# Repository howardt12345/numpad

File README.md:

# [numpad](https://kb.ht12345.xyz/np0)
[![CC BY-NC-SA 4.0][cc-by-nc-sa-shield]][cc-by-nc-sa]

### Numpad with alt key, 2 rotary encoders, and OLED display. Designed to be used with a pro micro.

## Specs:
- 2 Rotary Encoders
- 128x64 OLED display
- Per-key RGB matrix lighting
- Kailh Hotswap sockets
- QMK and Vial support

---
[The layout on keyboard layout editor](http://www.keyboard-layout-editor.com/#/gists/e6918e3b4176bcc28b69d0d3c7fc73e4)
[Photo gallery on @howardt12345](https://www.instagram.com/p/CbOJYpYOiaQ/)
[QMK (Pro Micro)](https://github.com/howardt12345/qmk_firmware/tree/ht12345/numpad/keyboards/ht12345/numpad)
[Vial (Pro Micro, KB2040)](https://github.com/howardt12345/vial-qmk/tree/ht12345/numpad/keyboards/ht12345/numpad)

---
## All of the files in this repository, including the PCBs, are provided without liability and without any guarantee with regards to functionality. Any production files and prototypes from this project are provided without warranty of any kind.

---

**This work is licensed under a** [Creative Commons Attribution-NonCommercial-ShareAlike 4.0 International License][cc-by-nc-sa].

[![CC BY-NC-SA 4.0][cc-by-nc-sa-image]][cc-by-nc-sa]

[cc-by-nc-sa]: http://creativecommons.org/licenses/by-nc-sa/4.0/
[cc-by-nc-sa-image]: https://licensebuttons.net/l/by-nc-sa/4.0/88x31.png
[cc-by-nc-sa-shield]: https://img.shields.io/badge/License-CC%20BY--NC--SA%204.0-lightgrey.svg

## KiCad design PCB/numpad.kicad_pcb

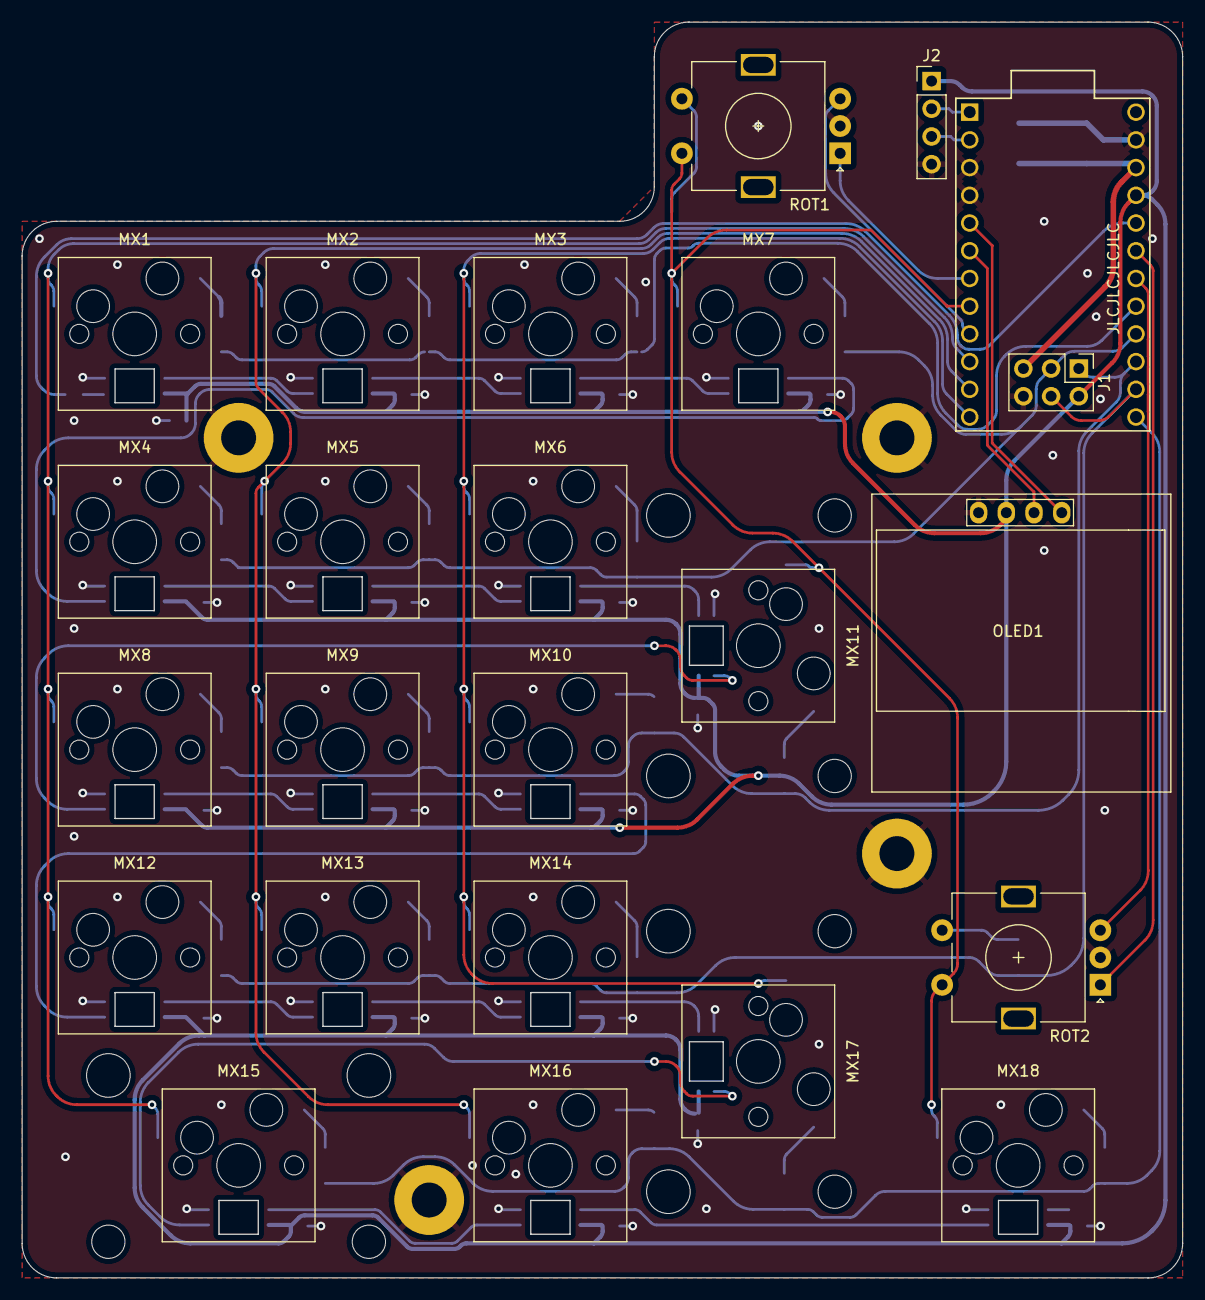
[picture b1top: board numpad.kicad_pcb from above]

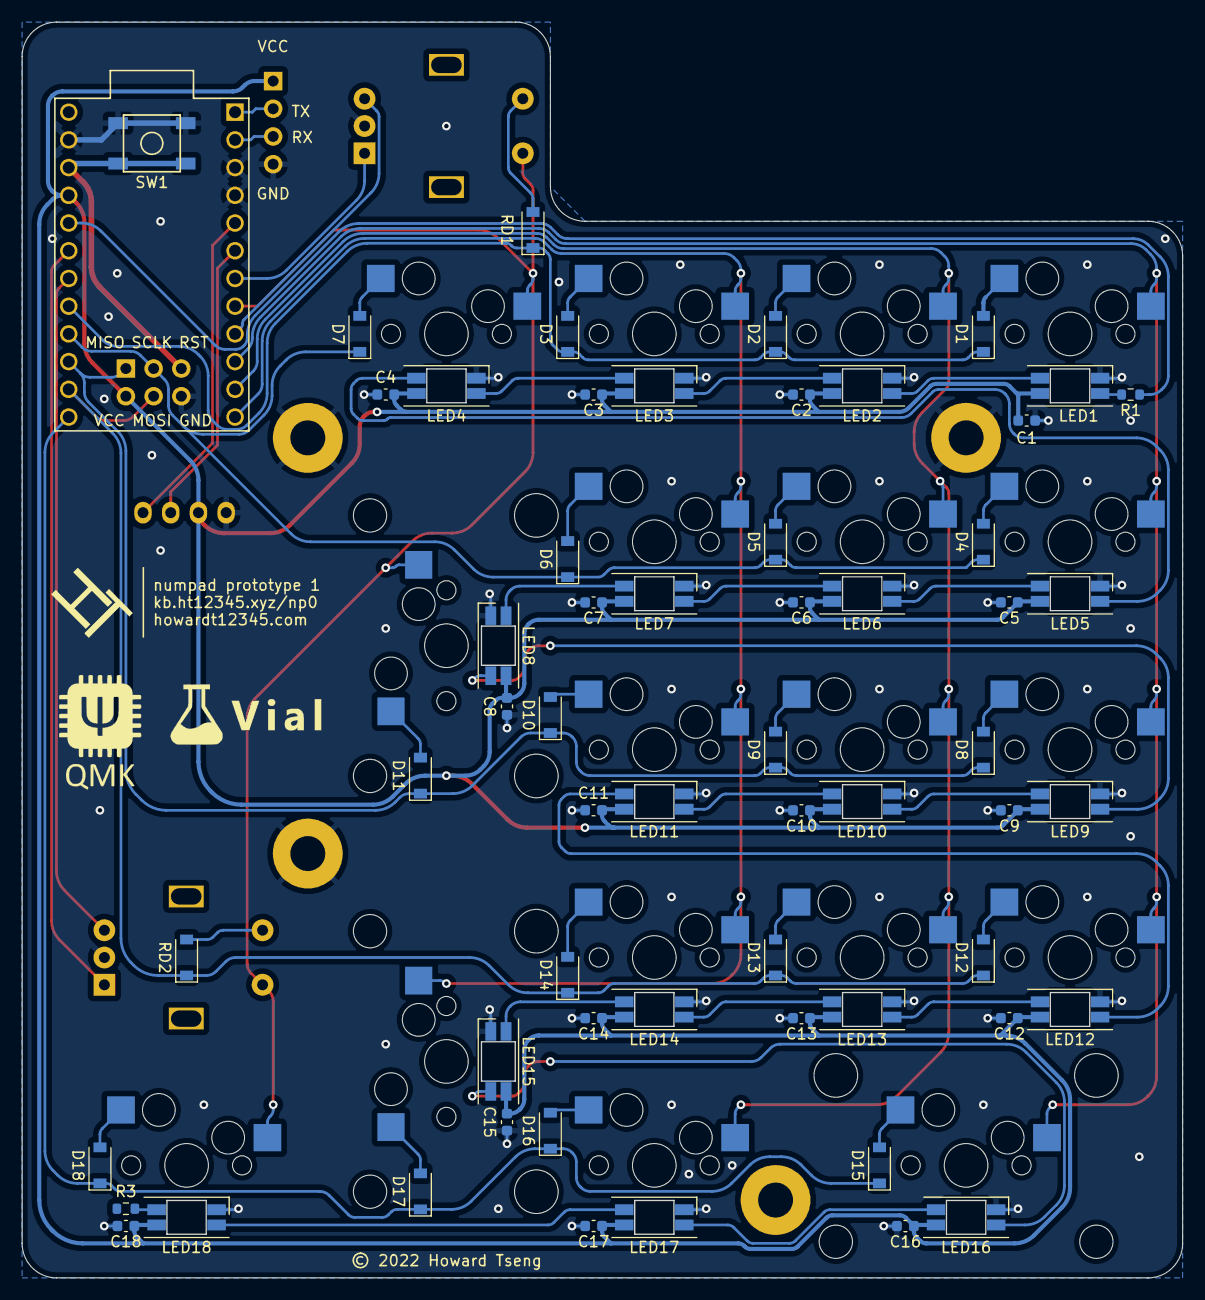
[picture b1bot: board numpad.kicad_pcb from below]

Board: 2 copper layers, 106.3 x 115.0 mm, 90 parts (61 on the bottom side), 60 nets.

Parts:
C1, C2, C3, C4, C5, C6, C7, C8, C9, C10, C11, C12, C13, C14, C15, C16, C17, C18: 100nF; C_0603_1608Metric
D1, D2, D3, D4, D5, D6, D7, D8, D9, D10, D11, D12, D13, D14, D15, D16, D17, D18: D_Small; D_SOD-123
H1, H2, H3, H4: M3; MountingHole_3.2mm_M3_Pad
J1: AVR-ISP-6; PinHeader_2x03_P2.54mm_Vertical
J2: Conn_01x04_Female; PinHeader_1x04_P2.54mm_Vertical
LED1, LED2, LED3, LED4, LED5, LED6, LED7, LED8, LED9, LED10, LED11, LED12, LED13, LED14, LED15, LED16, LED17, LED18: SK6812MINI-E; YS-SK6812MINI-E
LOGO1: Logo_Open_Hardware_Small; logo
LOGO2: Logo_Open_Hardware_Small; qmk_logo
LOGO3: Logo_Open_Hardware_Small; vial_logo
MX1, MX2, MX3, MX4, MX5, MX6, MX7, MX8, MX9, MX10, MX12, MX13, MX14, MX16: CherryMX; CherryMX_1.00u_PCB_KailhSocket
MX11, MX17: CherryMX; CherryMX_2.00u_PCB_KailhSocket_StabWireBottom
MX15: CherryMX; CherryMX_2.00u_PCB_KailhSocket_StabWireTop
MX18: CherryMX; CherryMX_1.50u_PCB_KailhSocket
OLED1: SSD1306; 128x64OLED
R1, R3: 470; R_0603_1608Metric
RD1, RD2: D_Small; D_SOD-123
ROT1, ROT2: Rotary_Encoder_Switch; RotaryEncoder_Alps_EC11E-Switch_Vertical_H20mm
SW1: SW_Push; SKQG-1155865
U1: ProMicro

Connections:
+5V: C1.1, C2.1, C3.1, C4.1, C5.1, C6.1, C7.1, C8.1, C9.1, C10.1, C11.1, C12.1, C13.1, C14.1, C15.1, C16.1, C17.1, C18.1, J1.2 (VCC), J2.1, LED1.1 (VDD), LED2.1 (VDD), LED3.1 (VDD), LED4.1 (VDD), LED5.1 (VDD), LED6.1 (VDD), LED7.1 (VDD), LED8.1 (VDD), LED9.1 (VDD), LED10.1 (VDD), LED11.1 (VDD), LED12.1 (VDD), LED13.1 (VDD), LED14.1 (VDD), LED15.1 (VDD), LED16.1 (VDD), LED17.1 (VDD), LED18.1 (VDD), OLED1.2 (VCC), U1.21 (VCC)
BKL_DATA_IN: R1.1, U1.20 (F4)
COL0: MX1.1, MX4.1, MX8.1, MX12.1, MX15.1, U1.10 (E6)
COL1: MX2.1, MX5.1, MX9.1, MX13.1, MX16.1, U1.11 (B4)
COL2: MX3.1, MX6.1, MX10.1, MX14.1, MX17.1, U1.12 (B5)
COL3: MX7.1, MX11.1, MX18.1, ROT1.S2, ROT2.S2, U1.8 (C6)
ENC_A1: ROT1.A, U1.7 (D4)
ENC_A2: ROT2.A, U1.19 (F5)
ENC_B1: ROT1.B, U1.9 (D7)
ENC_B2: ROT2.B, U1.18 (F6)
GND: C1.2, C2.2, C3.2, C4.2, C5.2, C6.2, C7.2, C8.2, C9.2, C10.2, C11.2, C12.2, C13.2, C14.2, C15.2, C16.2, C17.2, C18.2, H1.1, H2.1, H3.1, H4.1, J1.6 (GND), J2.4, LED1.3 (VSS), LED2.3 (VSS), LED3.3 (VSS), LED4.3 (VSS), LED5.3 (VSS), LED6.3 (VSS), LED7.3 (VSS), LED8.3 (VSS), LED9.3 (VSS), LED10.3 (VSS), LED11.3 (VSS), LED12.3 (VSS), LED13.3 (VSS), LED14.3 (VSS), LED15.3 (VSS), LED16.3 (VSS), LED17.3 (VSS), LED18.3 (VSS), OLED1.1 (GND), ROT1.C, ROT2.C, SW1.2, U1.3 (GND), U1.4 (GND), U1.23 (GND)
MISO: D8.1 (K), D9.1 (K), D10.1 (K), D11.1 (K), J1.1 (MISO), U1.15 (B3)
MOSI: D12.1 (K), D13.1 (K), D14.1 (K), J1.4 (MOSI), RD2.1 (K), U1.14 (B2)
unnamed: D1.2 (A), MX1.2
unnamed: D2.2 (A), MX2.2
unnamed: D3.2 (A), MX3.2
unnamed: D4.2 (A), MX4.2
unnamed: D5.2 (A), MX5.2
unnamed: D6.2 (A), MX6.2
unnamed: D7.2 (A), MX7.2
unnamed: D8.2 (A), MX8.2
unnamed: D9.2 (A), MX9.2
unnamed: D10.2 (A), MX10.2
unnamed: D11.2 (A), MX11.2
unnamed: D12.2 (A), MX12.2
unnamed: D13.2 (A), MX13.2
unnamed: D14.2 (A), MX14.2
unnamed: D15.2 (A), MX15.2
unnamed: D16.2 (A), MX16.2
unnamed: D17.2 (A), MX17.2
unnamed: D18.2 (A), MX18.2
unnamed: LED1.2 (DOUT), LED2.4 (DIN)
unnamed: LED1.4 (DIN), R1.2
unnamed: LED2.2 (DOUT), LED3.4 (DIN)
unnamed: LED3.2 (DOUT), LED4.4 (DIN)
unnamed: LED4.2 (DOUT), LED5.4 (DIN)
unnamed: LED5.2 (DOUT), LED6.4 (DIN)
unnamed: LED6.2 (DOUT), LED7.4 (DIN)
unnamed: LED7.2 (DOUT), LED8.4 (DIN)
unnamed: LED8.2 (DOUT), LED9.4 (DIN)
unnamed: LED10.2 (DOUT), LED11.4 (DIN)
unnamed: LED9.2 (DOUT), LED10.4 (DIN)
unnamed: LED11.2 (DOUT), LED12.4 (DIN)
unnamed: LED12.2 (DOUT), LED13.4 (DIN)
unnamed: LED13.2 (DOUT), LED14.4 (DIN)
unnamed: LED14.2 (DOUT), LED15.4 (DIN)
unnamed: LED15.2 (DOUT), LED16.4 (DIN)
unnamed: LED16.2 (DOUT), LED17.4 (DIN)
unnamed: LED17.2 (DOUT), LED18.4 (DIN)
unnamed: LED18.2 (DOUT), R3.1
unnamed: RD1.2 (A), ROT1.S1
unnamed: RD2.2 (A), ROT2.S1
ROW0: D1.1 (K), D2.1 (K), D3.1 (K), RD1.1 (K), U1.17 (F7)
ROW1: D4.1 (K), D5.1 (K), D6.1 (K), D7.1 (K), J1.3 (SCK), U1.16 (B1)
ROW4: D15.1 (K), D16.1 (K), D17.1 (K), D18.1 (K), U1.13 (B6)
RST: J1.5 (~RST), SW1.1, U1.22 (RST)
RX: J2.3, U1.2 (RX)
SCL: OLED1.3 (SCL), U1.6 (SCL)
SDA: OLED1.4 (SDA), U1.5 (SDA)
TX: J2.2, U1.1 (TX)

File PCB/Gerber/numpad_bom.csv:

Comment,Designator,Footprint,LCSC
100nF,"C1,C10,C11,C12,C13,C14,C15,C16,C17,C18,C2,C3,C4,C5,C6,C7,C8,C9",C_0603_1608Metric,C14663
470,"R1,R3",R_0603_1608Metric,C23179
SW_Push,SW1,SKQG-1155865,C318884
SK6812MINI-E,"LED1,LED10,LED11,LED12,LED13,LED14,LED15,LED16,LED17,LED18,LED2,LED3,LED4,LED5,LED6,LED7,LED8,LED9",YS-SK6812MINI-E,C524051
D_Small,"D1,D10,D11,D12,D13,D14,D15,D16,D17,D18,D2,D3,D4,D5,D6,D7,D8,D9,RD1,RD2",D_SOD-123,C81598

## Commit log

2021-11-20 Laid out the basic layout
2021-11-21 Switched to Pro Micro
2021-11-21 Refined traces and schematic for review
2021-11-21 Moved a via
2021-11-21 Schematic pic export
2021-11-21 Exported gerber
2021-11-22 Added mounting holes
2021-11-22 Adjusted plate outline
2021-11-22 Moved microcontroller by 1/4U
2021-11-22 Moved microcontroller
2021-11-22 Exported gerbers
2021-11-22 Exported proper gerber files for plate
2021-11-22 Updated gerber export settings
2021-12-25 Cleaned up traces
2022-01-14 Polished routing
2022-01-16 Added logos, cleaned up routing
2022-01-16 Moved order number and exported production gerbers
2022-01-16 Removed ground fill from plate
2022-01-16 numpad case 3d model
2022-01-16 Update fp-info-cache
2022-02-02 Updated to kicad 6
2022-02-03 Completely redid schematic and PCB
2022-02-03 Cleanup and exported gerbers
2022-02-03 Set up JLCPCB plugin
2022-02-03 Added 3d models, cleaned up traces, exported gerbers
2022-02-03 zipped gerbers
2022-02-04 Curved more traces
2022-02-04 Adjusted traces
2022-02-14 Experimented with EVQWGD001 footprint
2022-02-14 changed plate url text
2022-02-14 exported for production
2022-03-26 updated case file
2022-03-26 Updated numpad switch labels
2022-03-26 readme and license
2022-05-13 Extended bottom by 1mm

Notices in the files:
PCB/numpad.kicad_pcb:
© 2022 Howard Tseng
